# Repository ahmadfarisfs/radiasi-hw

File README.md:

# radiasi-hw
Repo for Smart UV Bottle Exposure PCB and hardware design

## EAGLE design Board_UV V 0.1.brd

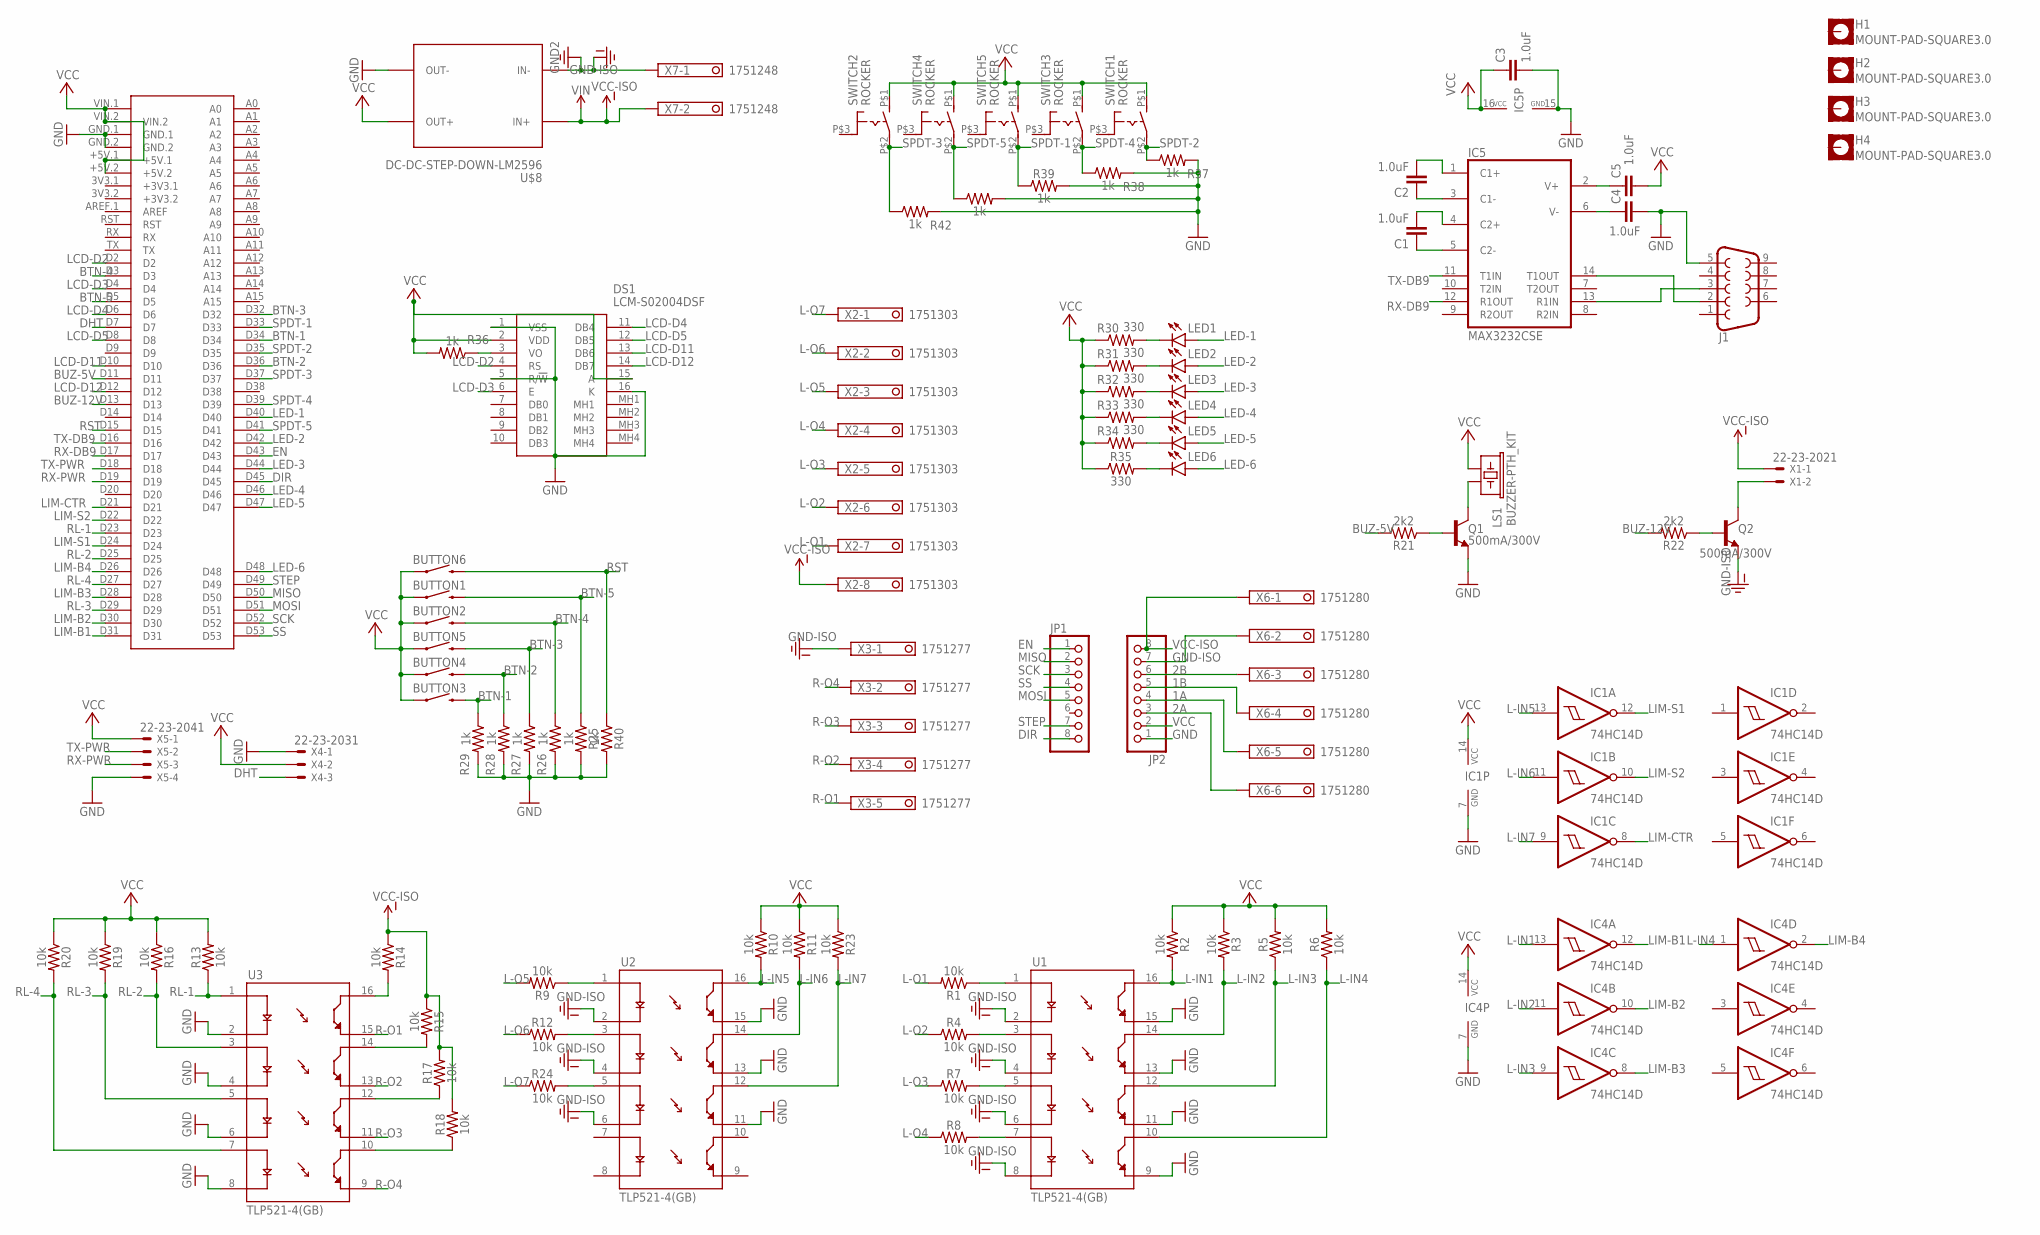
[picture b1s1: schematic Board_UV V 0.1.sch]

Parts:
BUTTON1, BUTTON2, BUTTON3, BUTTON4, BUTTON5, BUTTON6: MOMENTARY-SWITCH-SPST-PTH-12MM; TACTILE_SWITCH_PTH_12MM
C1, C2, C3, C4, C5: 1.0uF; 0603
DS1: LCM-S02004DSF; LCMS02004DSF
H1, H2, H3, H4: MOUNT-PAD-SQUARE3.0; 3,0-PAD-SQUARE
IC1, IC4: 74HC14D; SO14
IC5: MAX3232CSE; SO16
J1: DB9FEMALE; DB9
JP1, JP2: PINHD-1X8; 1X08
LED1, LED2, LED3, LED4, LED5, LED6: LED5MM
LS1: BUZZER-PTH_KIT; BUZZER-12MM-KIT
Q1, Q2: 500mA/300V; SOT23-3
R1, R2, R3, R4, R5, R6, R7, R8, R9, R10, R11, R12, R13, R14, R15, R16, R17, R18, R19, R20, R23, R24: 10k; 0603
R21, R22: 2k2; 0603
R25, R26, R27, R28, R29, R36, R37, R38, R39, R40, R41, R42: 1k; 0603
R30, R31, R32, R33, R34, R35: 330; 0603
SWITCH1, SWITCH2, SWITCH3, SWITCH4, SWITCH5: ROCKER; 320-916
U1, U2, U3: TLP521-4(GB); DIP762W50P254L2007H485Q16
U$1: MEGA2560_MIKRO
U$8: DC-DC-STEP-DOWN-LM2596
X1: 22-23-2021
X2: 1751303
X3: 1751277
X4: 22-23-2031
X5: 22-23-2041
X6: 1751280
X7: 1751248

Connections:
1A: JP2.4, X6.5
1B: JP2.5, X6.4
2A: JP2.3, X6.6
2B: JP2.6, X6.3
BTN-1: BUTTON3.3 (2), R29.1, U$1.D34
BTN-2: BUTTON4.3 (2), R28.1, U$1.D36
BTN-3: BUTTON5.3 (2), R27.1, U$1.D32
BTN-4: BUTTON2.3 (2), R26.1, U$1.D3
BTN-5: BUTTON1.3 (2), R25.1, U$1.D5
BUZ-5V: R21.2, U$1.D11
BUZ-12V: R22.2, U$1.D13
DHT: U$1.D7, X4.3
DIR: JP1.8, U$1.D45
EN: JP1.1, U$1.D43
GND: C3.2, C4.2, DS1.1 (VSS), DS1.5 (R/!W), DS1.16 (K), IC1.7 (GND), IC4.7 (GND), IC5.15 (GND), J1.5, JP2.1, Q1.2 (E), R25.2, R26.2, R27.2, R28.2, R29.2, R37.2, R38.2, R39.2, R40.2, R41.2, R42.2, U1.9 (ET4), U1.11 (ET3), U1.13 (ET2), U1.15 (ET1), U2.11 (ET3), U2.13 (ET2), U2.15 (ET1), U3.2 (C1), U3.4 (C2), U3.6 (C3), U3.8 (C4), U$1.GND.1, U$1.GND.2, U$8.OUT-, X4.1, X5.4
GND-ISO: JP2.7, Q2.2 (E), U1.2 (C1), U1.4 (C2), U1.6 (C3), U1.8 (C4), U2.2 (C1), U2.4 (C2), U2.6 (C3), U$8.IN-, X3.1, X6.2, X7.1
L-IN1: IC4.13 (I), R2.2, U1.16 (CT1)
L-IN2: IC4.11 (I), R3.2, U1.14 (CT2)
L-IN3: IC4.9 (I), R5.1, U1.12 (CT3)
L-IN4: IC4.1 (I), R6.1, U1.10 (CT4)
L-IN5: IC1.13 (I), R10.2, U2.16 (CT1)
L-IN6: IC1.11 (I), R11.2, U2.14 (CT2)
L-IN7: IC1.9 (I), R23.2, U2.12 (CT3)
L-O1: R1.2, X2.7
L-O2: R4.1, X2.6
L-O3: R7.1, X2.5
L-O4: R8.1, X2.4
L-O5: R9.2, X2.3
L-O6: R12.1, X2.2
L-O7: R24.1, X2.1
LCD-D2: DS1.4 (RS), U$1.D2
LCD-D3: DS1.6 (E), U$1.D4
LCD-D4: DS1.11 (DB4), U$1.D6
LCD-D5: DS1.12 (DB5), U$1.D8
LCD-D11: DS1.13 (DB6), U$1.D10
LCD-D12: DS1.14 (DB7), U$1.D12
LED-1: LED1.A, U$1.D40
LED-2: LED2.A, U$1.D42
LED-3: LED3.A, U$1.D44
LED-4: LED4.A, U$1.D46
LED-5: LED5.A, U$1.D47
LED-6: LED6.A, U$1.D48
LIM-B1: IC4.12 (O), U$1.D31
LIM-B2: IC4.10 (O), U$1.D30
LIM-B3: IC4.8 (O), U$1.D28
LIM-B4: IC4.2 (O), U$1.D26
LIM-CTR: IC1.8 (O), U$1.D21
LIM-S1: IC1.12 (O), U$1.D24
LIM-S2: IC1.10 (O), U$1.D22
MISO: JP1.2, U$1.D50
MOSI: JP1.5, U$1.D51
unnamed: C1.1, IC5.5 (C2-)
unnamed: C4.1, IC5.6 (V-)
unnamed: C2.1, IC5.3 (C1-)
unnamed: C2.2, IC5.1 (C1+)
unnamed: C1.2, IC5.4 (C2+)
unnamed: IC5.14 (T1OUT), J1.2
unnamed: C5.1, IC5.2 (V+)
unnamed: LED1.K (C), R30.2
unnamed: LED4.K (C), R33.2
unnamed: IC5.13 (R1IN), J1.3
unnamed: R1.1, U1.1 (A1)
unnamed: R4.2, U1.3 (A2)
unnamed: R7.2, U1.5 (A3)
unnamed: R8.2, U1.7 (A4)
unnamed: R9.1, U2.1 (A1)
unnamed: R12.2, U2.3 (A2)
unnamed: Q1.1 (B), R21.1
unnamed: R14.2, U3.16 (CT1)
unnamed: R15.2, U3.14 (CT2)
unnamed: R17.1, U3.12 (CT3)
unnamed: R18.1, U3.10 (CT4)
unnamed: LS1.- (2), Q1.3 (C)
unnamed: Q2.3 (C), X1.2
unnamed: DS1.3 (VO), R36.1
unnamed: Q2.1 (B), R22.1
unnamed: R24.2, U2.5 (A3)
unnamed: LED2.K (C), R31.2
unnamed: LED3.K (C), R32.2
unnamed: LED5.K (C), R34.2
unnamed: LED6.K (C), R35.2
R-O1: U3.15 (ET1), X3.5
R-O2: U3.13 (ET2), X3.4
R-O3: U3.11 (ET3), X3.3
R-O4: U3.9 (ET4), X3.2
RL-1: R13.1, U3.1 (A1), U$1.D23
RL-2: R16.2, U3.3 (A2), U$1.D25
RL-3: R19.2, U3.5 (A3), U$1.D29
RL-4: R20.2, U3.7 (A4), U$1.D27
RST: BUTTON6.3 (2), R40.1, U$1.D15
RX-DB9: IC5.12 (R1OUT), U$1.D17
RX-PWR: U$1.D19, X5.3
SCK: JP1.3, U$1.D52
SPDT-1: R39.1, SWITCH5.P$2, U$1.D33
SPDT-2: R37.1, SWITCH1.P$2, U$1.D35
SPDT-3: R42.1, SWITCH2.P$2, U$1.D37
SPDT-4: R38.1, SWITCH3.P$2, U$1.D39
SPDT-5: R41.1, SWITCH4.P$2, U$1.D41
SS: JP1.4, U$1.D53
STEP: JP1.7, U$1.D49
TX-DB9: IC5.11 (T1IN), U$1.D16
TX-PWR: U$1.D18, X5.2
VCC: BUTTON1.1, BUTTON2.1, BUTTON3.1, BUTTON4.1, BUTTON5.1, BUTTON6.1, C3.1, C5.2, DS1.2 (VDD), DS1.15 (A), IC1.14 (VCC), IC4.14 (VCC), IC5.16 (VCC), JP2.2, LS1.+ (1), R2.1, R3.1, R5.2, R6.2, R10.1, R11.1, R13.2, R16.1, R19.1, R20.1, R23.1, R30.1, R31.1, R32.1, R33.1, R34.1, R35.1, R36.2, SWITCH1.P$1 (S), SWITCH2.P$1 (S), SWITCH3.P$1 (S), SWITCH4.P$1 (S), SWITCH5.P$1 (S), U$1.+5V.1, U$1.+5V.2, U$1.VIN.1, U$1.VIN.2, U$8.OUT+, X4.2, X5.1
VCC-ISO: JP2.8, R14.1, R15.1, R17.2, R18.2, U$8.IN+, X1.1, X2.8, X6.1, X7.2

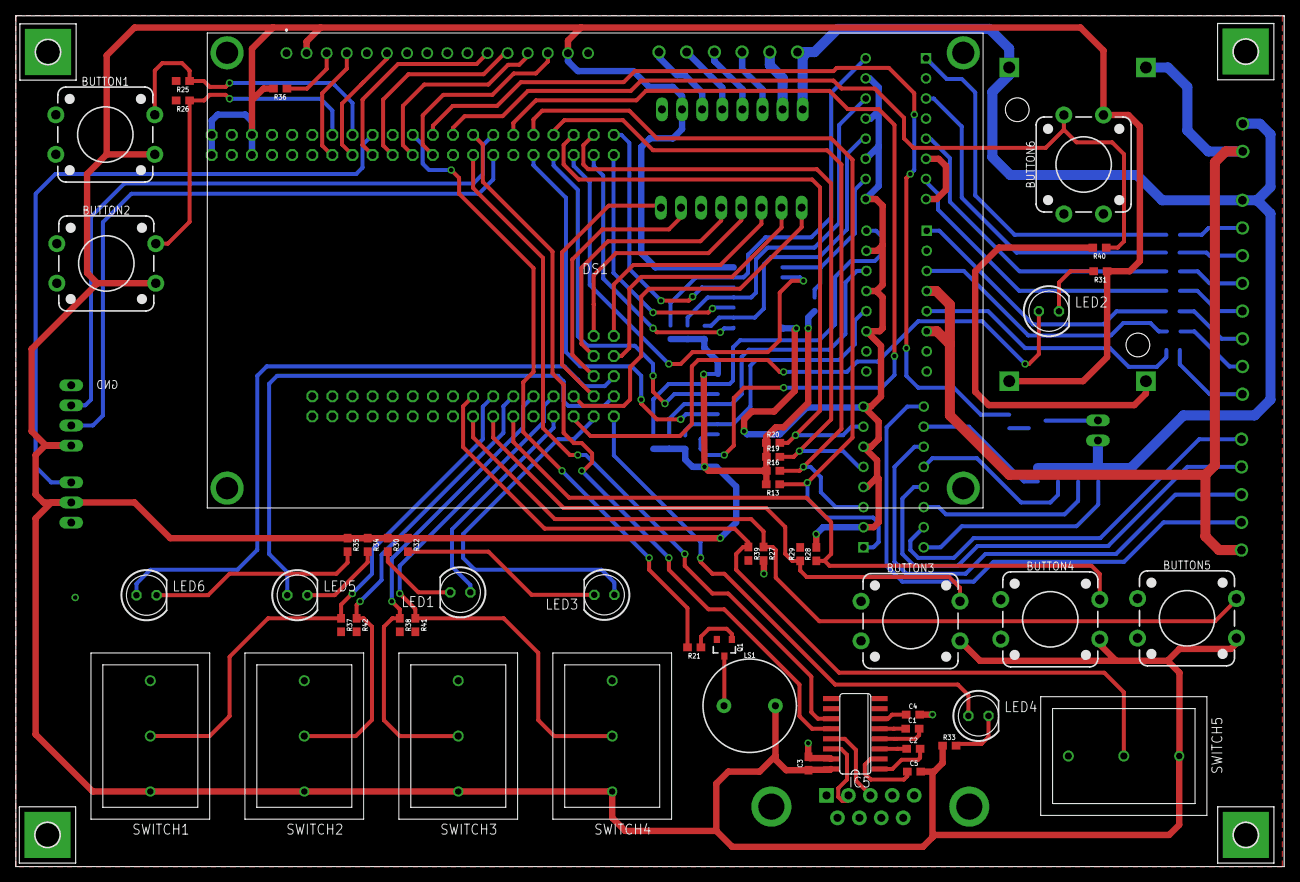
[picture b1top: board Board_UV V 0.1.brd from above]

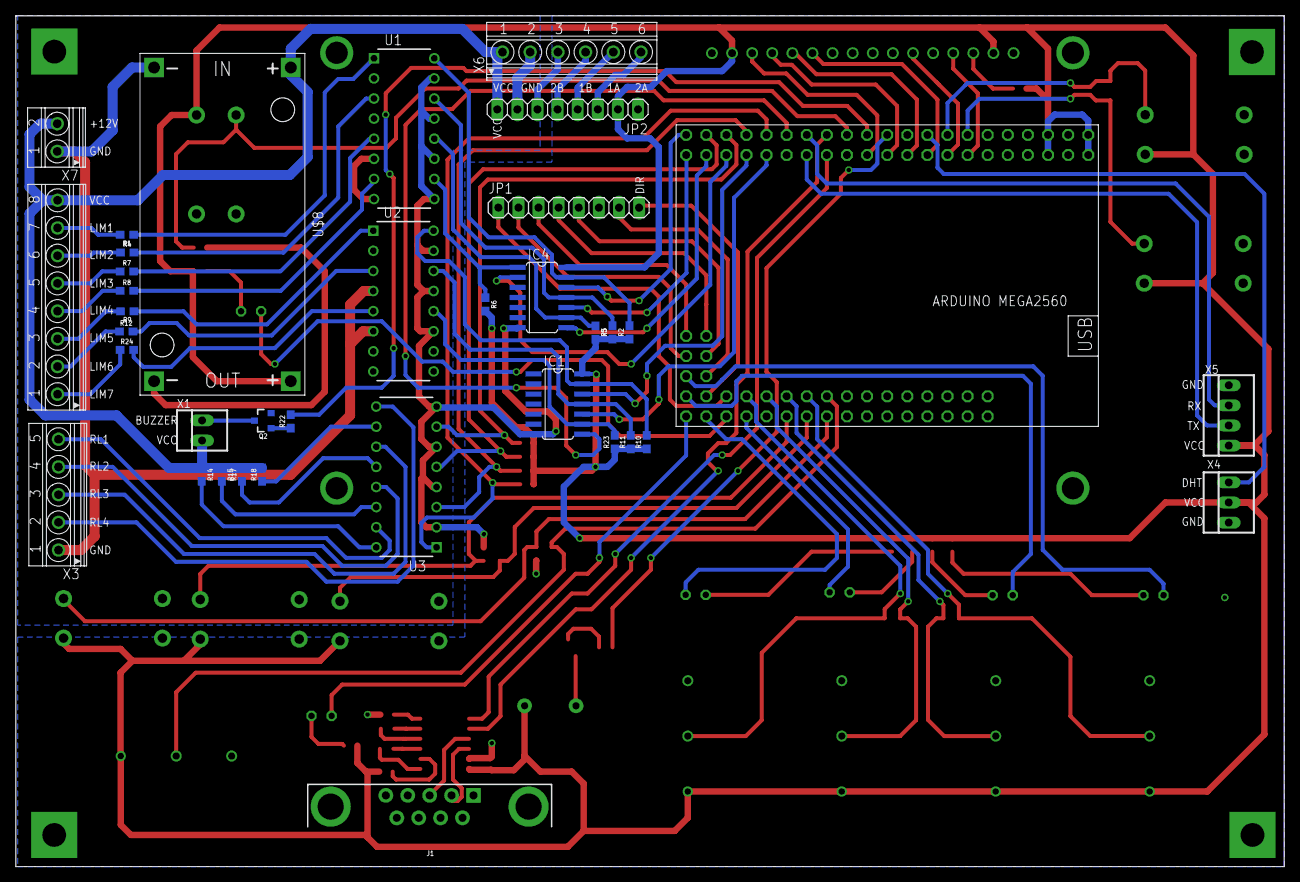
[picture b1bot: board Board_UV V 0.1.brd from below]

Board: 2 copper layers, 160.2 x 107.5 mm, 90 parts (37 on the bottom side), 104 nets.

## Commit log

2019-12-15 Initial design eagle
2019-12-17 Add other component
2020-01-06 add board design
2020-01-06 change button power reset
2020-01-11 finalisasi and add name
2020-02-04 last update

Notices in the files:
parts and their libraries:
SparkFun-Capacitors: Licensing: Creative Commons ShareAlike 4.0 International - https://creativecommons.org/licenses/by-sa/4.0
diy-modules: Released under the Creative Commons Attribution 4.0 International License: http://creativecommons.org/licenses/by/4.0
